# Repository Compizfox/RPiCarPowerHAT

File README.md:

# RPiCarPowerHAT
Automotive power management HAT for Raspberry Pi

The RPiCarPowerHAT is power management circuit for the Raspberry Pi in the form of a HAT. It is designed to to power a Raspberry Pi from 12 V available in a car. It uses a buck converter as a power supply and includes a power management circuit that powers the RPi by the car's permanent power (BAT), but can be switched by the car's accessory power (ACC) and subsequently latched by a GPIO pin from the RPi (inspired by [CarPiHat](https://github.com/gecko242/CarPiHat)). Hence, the RPi can be turned on using the car's ignition switch and latched on by the RPi itself so its power is not cut when the key is removed from the ignition. By releasing the latch, the RPi can then completely power itself down, in a software-defined way (for example, after a configurable time-out after removing the key from the ignition). This way, there is almost zero power draw when the RPi is turned off.

The RPiCarPowerHAT is designed to accept a LM2596 buck converter module, which can be found for less than €1. To alleviate coil whine and ripple, a post ripple filter consisting of an inductor and a capacitor (as recommended in [the datasheet](https://www.ti.com/lit/ds/symlink/lm2596.pdf)) is included in the HAT.

The board includes two opto-isolators for sensing 12 V, e.g. the car's ACC voltage and reversing voltage.

The board is fully THT for easy hand-soldering.

## Features
- Power supply: Uses a LM2596 buck converter module
  - Post ripple filter included
- Smart power management circuit:
  - The RPi is powered by the car's permanent 12 V power (BAT)
  - This is switched by a power MOSFET, which can be turned on by the car's ignition power (ACC) or latched from the RPi itself
  - Low-voltage cut-off to protect the car's battery from deeply discharging in case the RPi fails to release the latch
- 2 opto-isolated GPIO inputs, for e.g. sensing ACC voltage and reversing voltage
- 2 USB-A headers (power only), for e.g. powering a display
- A switched 12 V header for powering peripherals (powered when the RPi is)
- JST header with GND, BAT, ACC, and REV pins
- Status LEDs

## Circuit

## What you need to know
### GPIO pins (BCM numbering):
- Inputs:
  - BCM18 is pulled low when REV is high
  - BCM27 is pulled high wen ACC is high
- Outputs:
  - When BCM25 is pulled high from the RPi, it latches the power management circuit, causing it to stay on even when ACC is low.
  
### Tips
- Set the output voltage of the buck converter to 5.1 V by adjusting its trimpot before connecting the RPi, to prevent damaging the RPi by overvoltage.
- To set the low voltage threshold of the cut-off circuit, adjust trimpot RV1 on the board while measuring the voltage between TP1 and ground such that it reads 0.2 V at the desired threshold supply voltage.
- Do not connect a power supply to the RPi's own micro-USB input while using the power supply on this board.
- This does not fully comply with Raspberry Pi's HAT spec (it doesn't have an ID EEPROM onboard for GPIO autoconfiguration), so this is not an official Raspberry Pi® HAT.

## References

### KiCAD symbols, footprints, and models:

- [RPI_Hat_Template](https://github.com/devbisme/RPi_Hat_Template)
- [LM2596 module](https://grabcad.com/library/lm2596-module-for-kicad-1)
- [Stacked USB-A header](https://octopart.com/61400826021-w%C3%BCrth+elektronik-8917796)

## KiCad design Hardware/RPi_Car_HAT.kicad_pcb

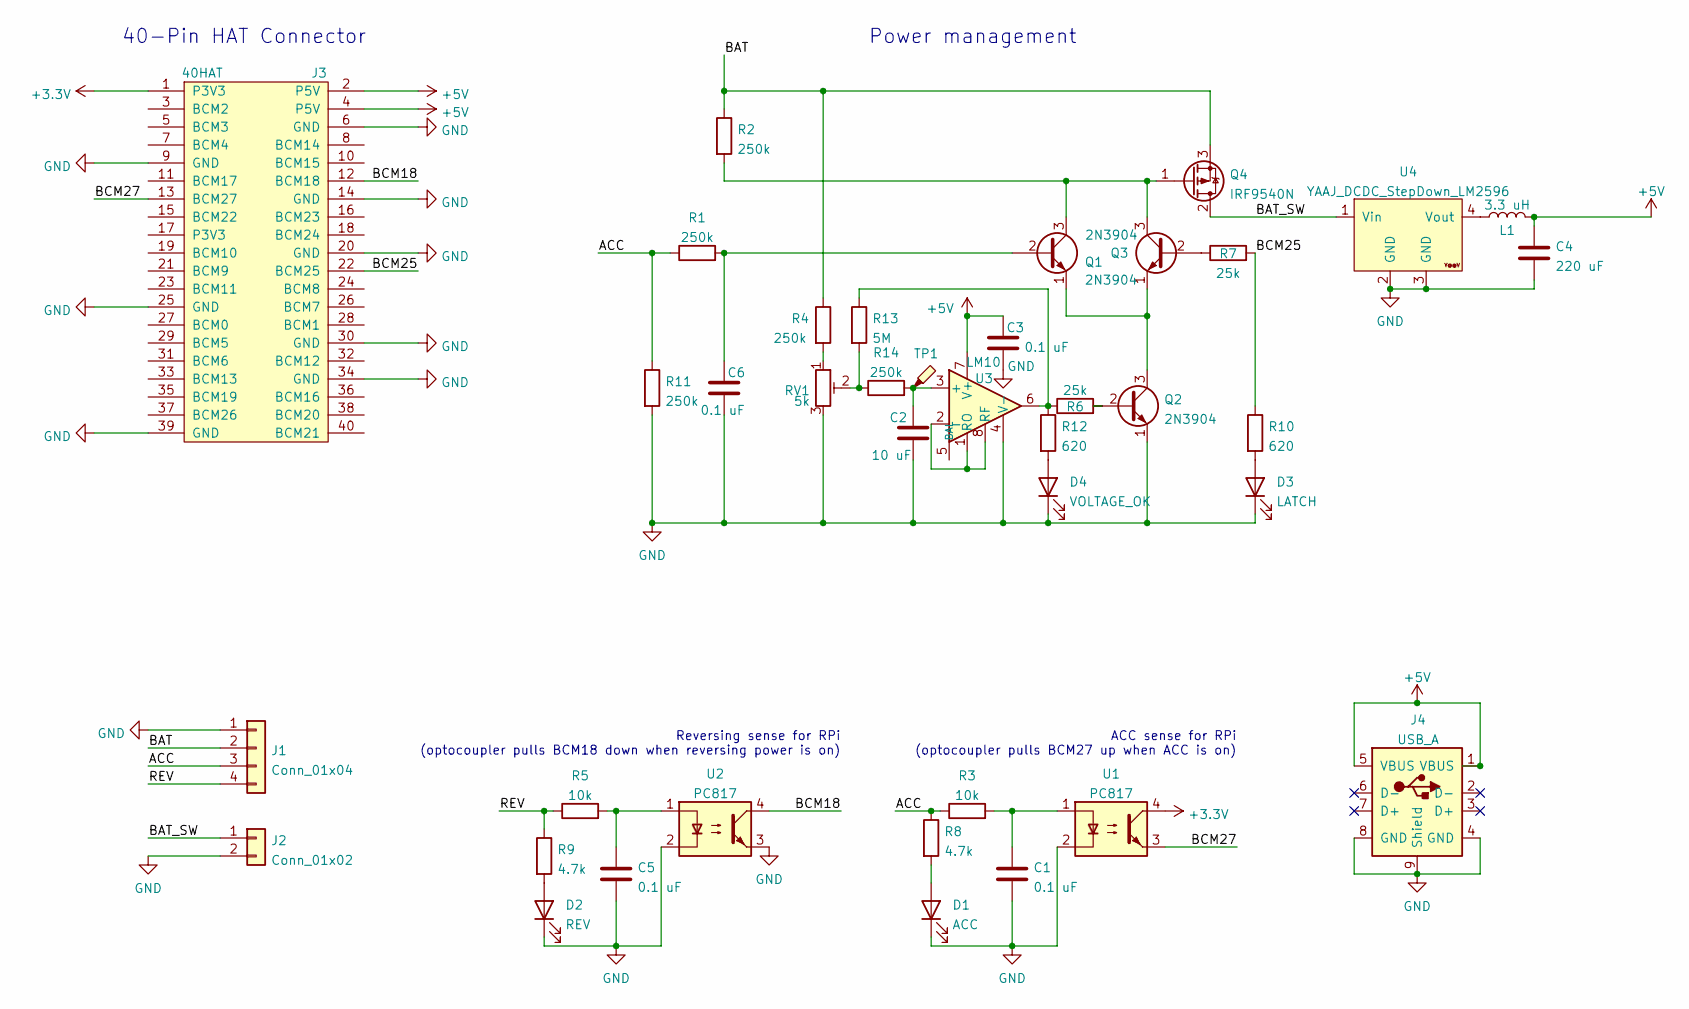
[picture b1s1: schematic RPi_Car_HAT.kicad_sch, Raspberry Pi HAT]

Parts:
C1, C3, C5, C6: 0.1 uF; C_Disc_D4.7mm_W2.5mm_P5.00mm
C2: 10 uF; C_Disc_D5.1mm_W3.2mm_P5.00mm
C4: 220 uF; CP_Radial_D6.3mm_P2.50mm
D1: ACC; LED_D3.0mm
D2: REV; LED_D3.0mm
D3: LATCH; LED_D3.0mm
D4: VOLTAGE_OK; LED_D3.0mm
J1: Conn_01x04; JST_XH_B4B-XH-A_1x04_P2.50mm_Vertical
J2: Conn_01x02; PinHeader_1x02_P2.54mm_Vertical
J3: 40HAT; PinSocket_2x20_P2.54mm_Vertical
J4: USB_A; USB_A_Wuerth_61400826021_Horizontal_Stacked
L1: 3.3 uH; L_Radial_D6.0mm_P4.00mm
Q1, Q2, Q3: 2N3904; TO-92_HandSolder
Q4: IRF9540N; TO-220-3_Vertical
R1, R2, R4, R11, R14: 250k; R_Axial_DIN0207_L6.3mm_D2.5mm_P7.62mm_Horizontal
R3, R5: 10k; R_Axial_DIN0207_L6.3mm_D2.5mm_P7.62mm_Horizontal
R6, R7: 25k; R_Axial_DIN0207_L6.3mm_D2.5mm_P7.62mm_Horizontal
R8, R9: 4.7k; R_Axial_DIN0207_L6.3mm_D2.5mm_P7.62mm_Horizontal
R10, R12: 620; R_Axial_DIN0207_L6.3mm_D2.5mm_P7.62mm_Horizontal
R13: 5M; R_Axial_DIN0207_L6.3mm_D2.5mm_P7.62mm_Horizontal
RV1: 5k; Potentiometer_Bourns_3296W_Vertical
TP1: TestPoint_Probe; TestPoint_THTPad_D1.0mm_Drill0.5mm
U1, U2: PC817; DIP-4_W7.62mm
U3: LM10; DIP-8_W7.62mm
U4: YAAJ_DCDC_StepDown_LM2596

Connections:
+3V3: J3.1 (P3V3), U1.4
+5V: C3.1, C4.1, J3.2 (P5V), J3.4 (P5V), J4.1 (VBUS), J4.5 (VBUS), L1.2, U3.7 (V+)
/ACC: J1.3, R1.1, R3.1, R8.1, R11.1
/BAT: J1.2, Q4.3 (S), R2.1, R4.1
/BAT_SW: J2.1, Q4.2 (D), U4.1 (Vin)
/BCM18: J3.12 (BCM18), U2.4
/BCM25: J3.22 (BCM25), R7.2, R10.1
/BCM27: J3.13 (BCM27), U1.3
/REV: J1.4, R5.1, R9.1
GND: C1.2, C2.2, C3.2, C4.2, C5.2, C6.2, D1.1 (K), D2.1 (K), D3.1 (K), D4.1 (K), J1.1, J2.2, J3.6 (GND), J3.9 (GND), J3.14 (GND), J3.20 (GND), J3.25 (GND), J3.30 (GND), J3.34 (GND), J3.39 (GND), J4.4 (GND), J4.8 (GND), J4.9 (Shield), Q2.1 (E), R11.2, RV1.3, U1.2, U2.2, U2.3, U3.4 (V-), U4.2 (GND), U4.3 (GND)
unnamed: C1.1, R3.2, U1.1
unnamed: C5.1, R5.2, U2.1
unnamed: D1.2 (A), R8.2
unnamed: D2.2 (A), R9.2
unnamed: D3.2 (A), R10.2
unnamed: D4.2 (A), R12.2
unnamed: C6.1, Q1.2 (B), R1.2
unnamed: Q1.3 (C), Q3.3 (C), Q4.1 (G), R2.2
unnamed: Q1.1 (E), Q2.3 (C), Q3.1 (E)
unnamed: Q2.2 (B), R6.2
unnamed: Q3.2 (B), R7.1
unnamed: R4.2, RV1.1
unnamed: R6.1, R12.1, R13.1, U3.6
unnamed: R13.2, R14.1, RV1.2
unnamed: C2.1, R14.2, TP1.1, U3.3 (+)
unnamed: U3.1 (RO), U3.2 (-), U3.8 (RF)
unnamed: L1.1, U4.4 (Vout)

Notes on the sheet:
ACC sense for RPi (optocoupler pulls BCM27 up when ACC is on)
Power management
40-Pin HAT Connector
Reversing sense for RPi (optocoupler pulls BCM18 down when reversing power is on)

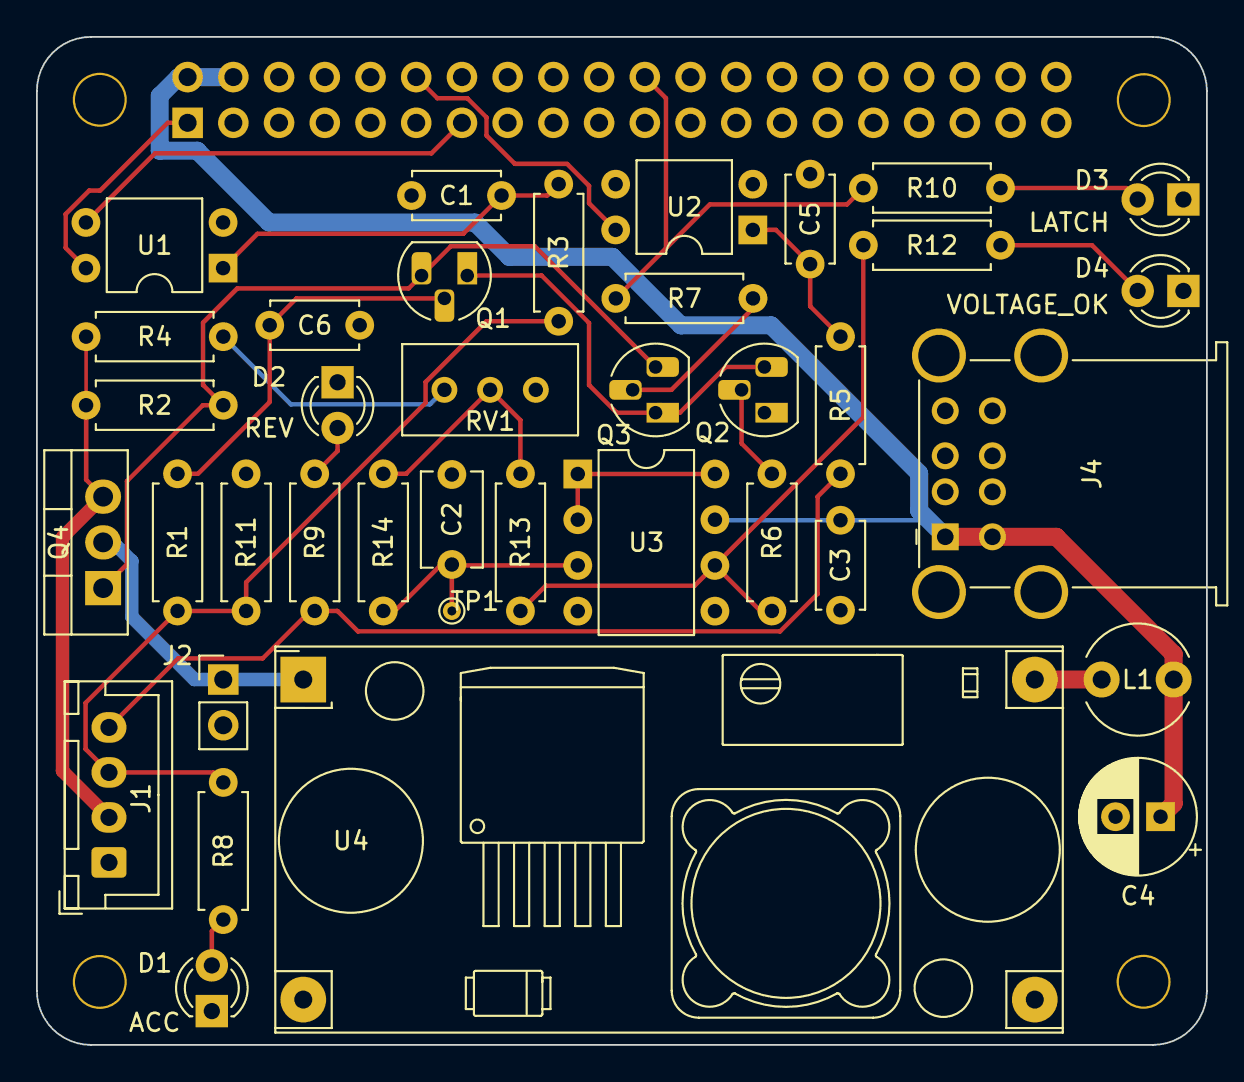
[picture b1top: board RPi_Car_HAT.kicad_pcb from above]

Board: 2 copper layers, 65.0 x 56.0 mm, 43 parts (1 on the bottom side), 27 nets.

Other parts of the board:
H1, H2, H3, H4: 3mm_Mounting_Hole; NPTH_3mm_ID

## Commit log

2021-12-04 Low voltage cut-off: add hysteresis, increase RC-time
2023-12-05 Put ACC trigger behind low voltage cut-off, update to new KiCAD version
2025-08-29 Revert "Put ACC trigger behind low voltage cut-off, update to new KiCAD version"
    This reverts commit 32efec27a2ba4a602edbb2af9725aed434bd226d.

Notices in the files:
Hardware/RPi_Car_HAT.kicad_pcb:
CERN-OHL-S
